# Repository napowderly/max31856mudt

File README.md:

# max31856mudt

Wooohooo a new package!

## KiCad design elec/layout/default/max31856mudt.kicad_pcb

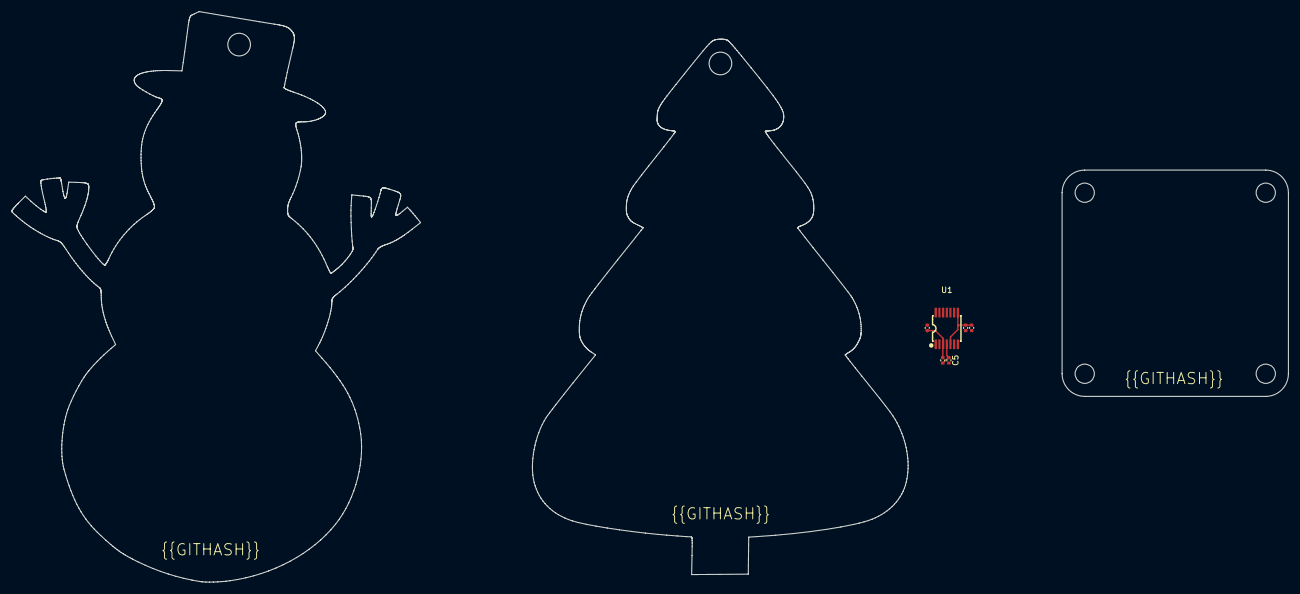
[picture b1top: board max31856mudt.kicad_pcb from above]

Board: 2 copper layers, 6 parts (0 on the bottom side), 4 nets.

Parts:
C1, C2, C3: Multilayer Ceramic Capacitors MLCC - SMD/SMT 100n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; C0402
C4, C5: Multilayer Ceramic Capacitors MLCC - SMD/SMT 22nF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; C0402
U1: TSSOP-14_L5.0-W4.4-P0.65-LS6.4-BL

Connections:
bias: C3.2, C5.1, U1.2, U1.4
gnd: C1.2, C2.2, C4.2, C5.2, U1.1, U1.14
vcc: C3.1, C4.1, U1.3
vcc-1: C1.1, C2.1, U1.5, U1.8

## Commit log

2024-02-13 Configure project
2024-02-14 added spi interfaces
